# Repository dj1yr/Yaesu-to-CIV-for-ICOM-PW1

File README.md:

The code is alpha, please note!

This small project translates the BCD code from Yaesu to ICOM CIV for communication with the PW1.

What do you have to do to make the PW1 work? First you have to teach the PW1 the address, this is in the manual, only with this solution you have to change the band until the LED on the remote is permanently on.

Now you have to know how the PW1 checks if the right subscriber can be reached, I will try to explain that.

When the PW1 is switched on and a participant has been programmed, the PW1 sends 6 bytes consisting of 0xFE,0xFE, address of participant, address PW1, 0x03,0xFD. The PW1 uses different data rates, from 0k6, 1k2, 2k4, 4k8, 9k6 and 19k2, at each data rate the query byte is sent 2x, the TRX must respond within 20ms, if not the next data rate is used, this is repeated 3x. If the TRX does not answer, the CIV communication is stopped, this can be retriggered by switching between TRX1 and TRX2 on the remote control, then the loop is restarted.

Now let's assume that the first communication worked, the first response from the TRX is structured as follows, 0xFE, 0xFE , address PW1, address TRX, 0x00 or 0x03, frequency data, 0xFD, then the PW1 switches to the received band.

Now the PW1 sends a new request every 10s, the CMD byte is initially 0x03, when the corresponding response comes, the PW1 sends 0x04, i.e. request for modulation. If one does not react to this, it can happen that the connection to the PW1 is interrupted, this also happened to me from time to time, so I send other answers.

I have developed a small board that fits into a SUBD15 connector housing, on the board an Atmega8 with TQFP32 housing is used, the Atmega 8 can of course be replaced by a pin compatible type.

In the development phase I am working with an Arduino Mega 2560 board.

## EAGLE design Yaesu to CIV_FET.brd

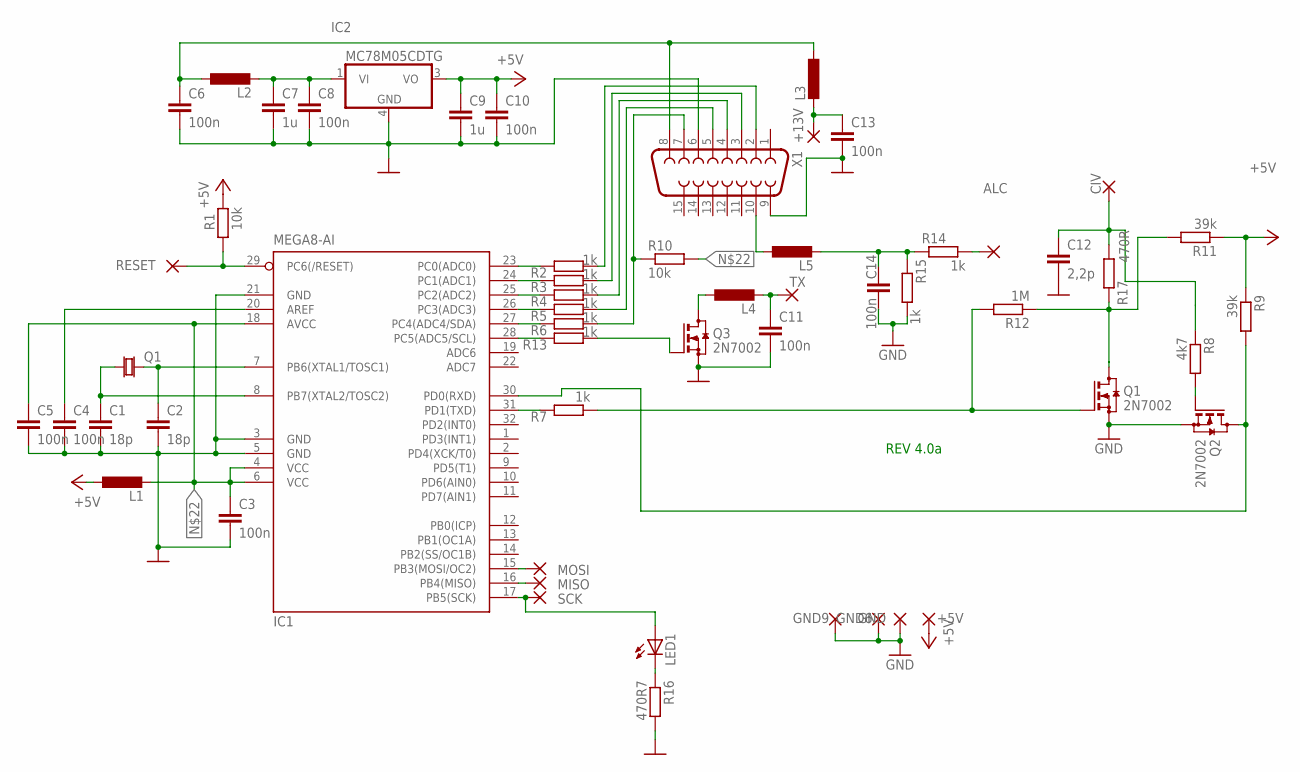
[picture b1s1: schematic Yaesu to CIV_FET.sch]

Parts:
+5V, +13V: SMD2; SMD1,27-2,54
ALC: SMD2; SMD1,27-2,54
C1, C2: 18p; C0603K
C3, C4, C5, C6, C8, C10, C11, C13, C14: 100n; C0603K
C7, C9: 1u; C0805K
C12: 2,2p; C0603K
CIV: SMD2; SMD1,27-2,54
GND, GND6, GND9: SMD2; SMD1,27-2,54
IC1: MEGA8-AI; TQFP32-08
IC2: MC78M05CDTG; DPACK_3
L1, L4, L5: L-EUL2012C; L2012C
L2, L3: L-EUL1812; L1812
LED1: LEDCHIP-LED0603; CHIP-LED0603
MISO: SMD2; SMD1,27-2,54
MOSI: SMD2; SMD1,27-2,54
Q1, Q2, Q3: 2N7002; SOT23
R1, R10: 10k; R0603
R2, R3, R4, R5, R6, R7, R13, R14, R15: 1k; R0603
R8: 4k7; R0603
R9, R11: 39k; R0603
R12: 1M; R0603
R16: 470R7; R0603
R17: 470R; R0603
RESET: SMD2; SMD1,27-2,54
SCK: SMD2; SMD1,27-2,54
TX: SMD2; SMD1,27-2,54
X1: F15D

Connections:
+5V: +5V.1, C9.1, C10.1, IC2.3 (VO), L1.1, R1.2, R9.1, R11.1
+13V: C6.1, L2.1, L3.1, X1.8
GND: C1.2, C2.2, C3.2, C4.2, C5.2, C6.2, C7.2, C8.2, C9.2, C10.2, C11.2, C12.2, C13.2, C14.2, GND.1, GND6.1, GND9.1, IC1.3 (GND), IC1.5 (GND), IC1.21 (GND), IC2.4 (GND), Q1.2 (S), Q2.2 (S), Q3.2 (S), R15.2, R16.2, X1.6, X1.9
unnamed: C2.1, IC1.7 (PB6(XTAL1/TOSC1))
unnamed: C1.1, IC1.8 (PB7(XTAL2/TOSC2))
unnamed: IC1.29 (PC6(/RESET)), R1.1, RESET.1
unnamed: IC1.23 (PC0(ADC0)), R2.2
unnamed: IC1.31 (PD1(TXD)), R7.2
unnamed: C4.1, IC1.20 (AREF)
unnamed: IC1.24 (PC1(ADC1)), R3.2
unnamed: IC1.25 (PC2(ADC2)), R4.2
unnamed: IC1.26 (PC3(ADC3)), R5.2
unnamed: R2.1, X1.2
unnamed: R3.1, X1.3
unnamed: R4.1, X1.4
unnamed: R5.1, X1.5
unnamed: IC1.27 (PC4(ADC4/SDA)), R6.2
unnamed: Q1.1 (G), R7.1, R12.2
unnamed: +13V.1, C13.1, L3.2
unnamed: C7.1, C8.1, IC2.1 (VI), L2.2
unnamed: R11.2, R12.1, R17.2
unnamed: L5.1, X1.10
unnamed: C3.1, C5.1, IC1.4 (VCC), IC1.6 (VCC), IC1.18 (AVCC), L1.2, R10.2
unnamed: IC1.28 (PC5(ADC5/SCL)), R13.2
unnamed: IC1.17 (PB5(SCK)), LED1.A, SCK.1
unnamed: IC1.16 (PB4(MISO)), MISO.1
unnamed: Q3.1 (G), R13.1
unnamed: L4.1, Q3.3 (D)
unnamed: ALC.1, R14.2
unnamed: IC1.15 (PB3(MOSI/OC2)), MOSI.1
unnamed: Q2.1 (G), R8.2
unnamed: IC1.30 (PD0(RXD)), Q2.3 (D), R9.2
unnamed: C14.1, L5.2, R14.1, R15.1
unnamed: C12.1, CIV.1, R8.1, R17.1
unnamed: LED1.C, R16.1
TX_IN: R6.1, R10.1, X1.7
TX_OUT: C11.1, L4.2, TX.1

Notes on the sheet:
REV 4.0a

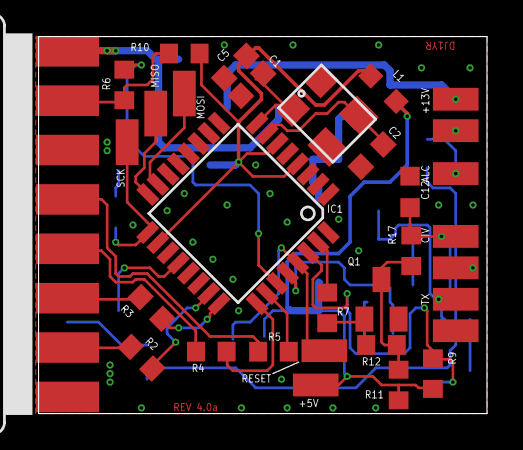
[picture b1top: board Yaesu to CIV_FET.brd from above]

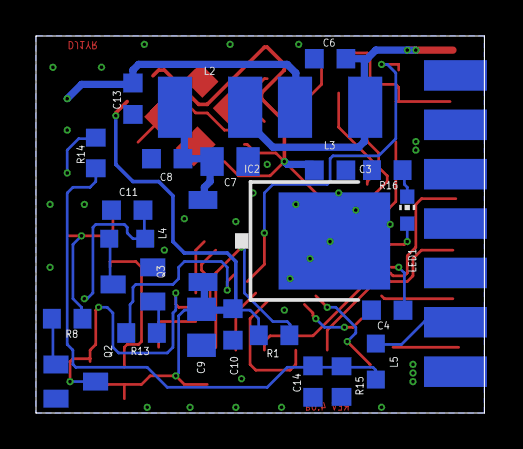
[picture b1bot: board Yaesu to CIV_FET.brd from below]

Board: 2 copper layers, 24.9 x 20.9 mm, 55 parts (24 on the bottom side), 37 nets.

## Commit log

2022-11-26 Create Board Files
